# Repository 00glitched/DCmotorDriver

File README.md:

# DCmotorDriver
BDC motor driver based on N-MOSFET transistors H-bridge

Logical supply:

- 3V to 6V

Bootstrap:

- 10V to 20V
- 0A to 2A (current peak)

Power supply:

- 10V to 80V
- 0A to 3A (5A with dissipation)

## Material list
POWER:

- Driver IR2110 x2
- D FR107 x2
- C100uF electrolytic - 50V x2
- C47nF - 50V x2
- MOSFET IRF540N (or 520) x4
- D FR102 x4
- R10 x4

OTHERS:

- BJT BC635 (to 639) x2
- R10k x6
- C10uF - 250V
- C10uF - 10V
- C100uF - 50V

## Topology
- Driver 1: left-high-side + right-low-side

- Driver 2: right-high-side + left-low-side

## Images

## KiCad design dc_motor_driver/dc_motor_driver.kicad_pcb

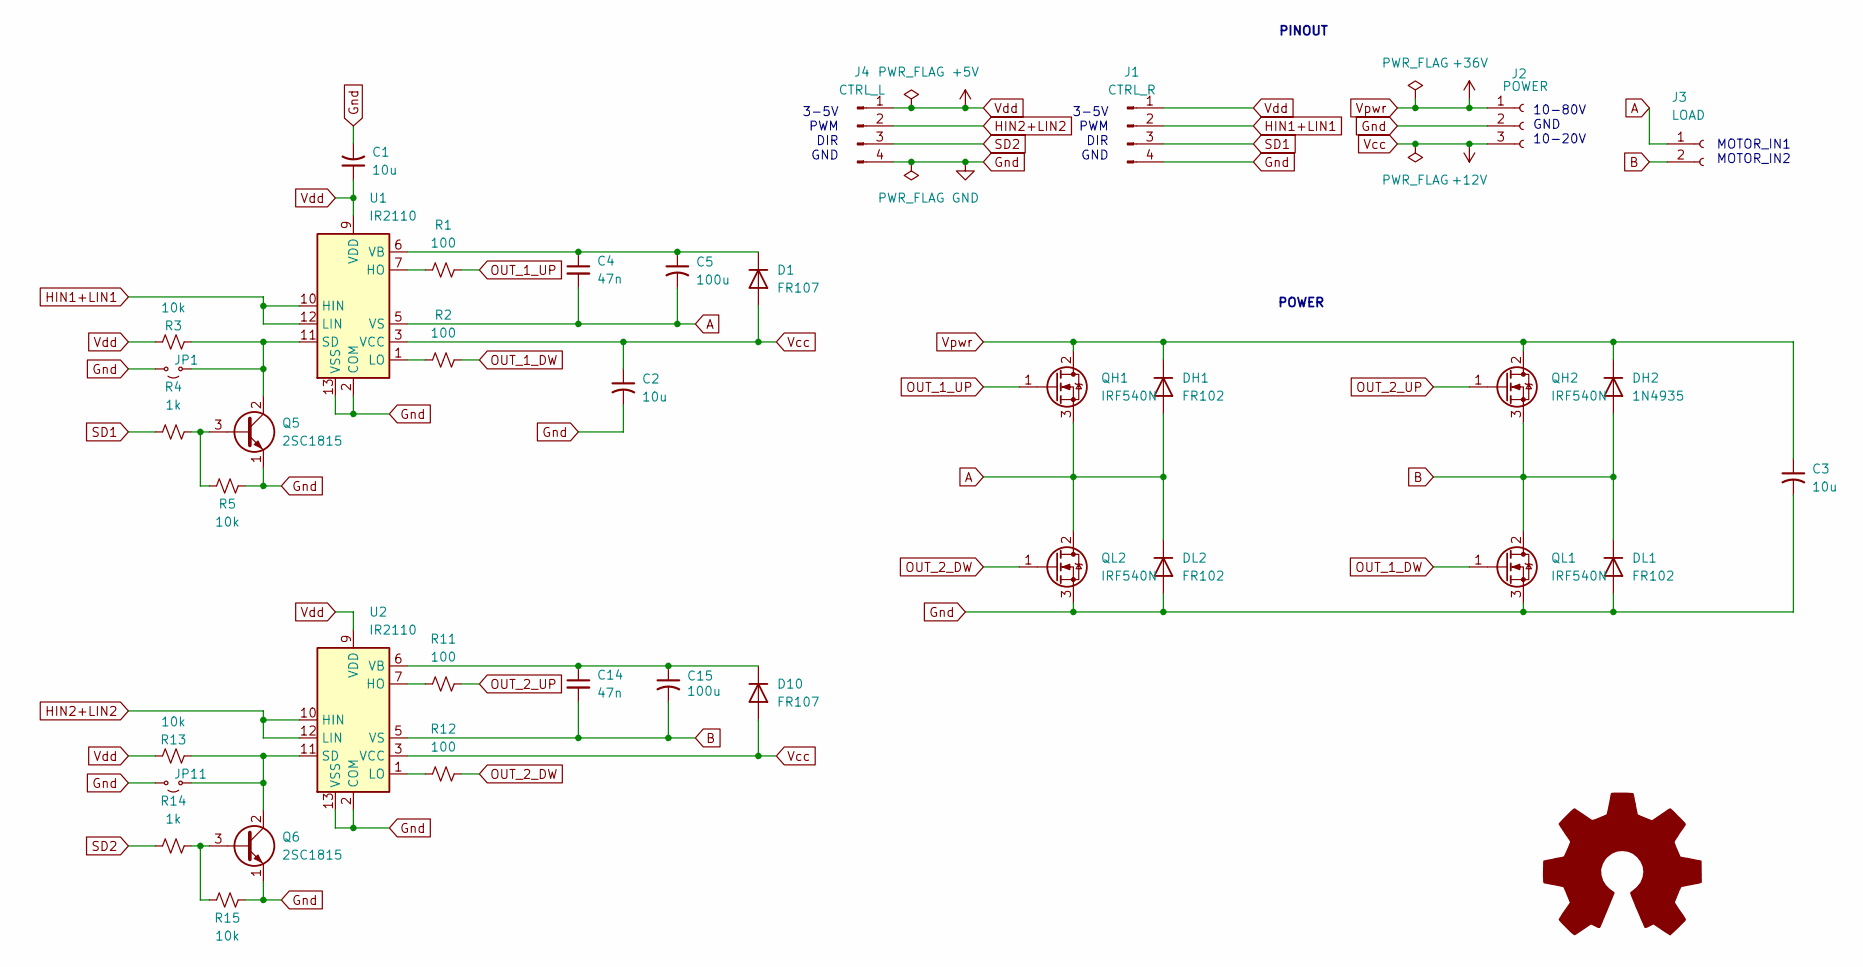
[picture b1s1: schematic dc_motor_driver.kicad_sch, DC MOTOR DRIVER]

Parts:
C1: 10u; CP_Radial_D5.0mm_P2.50mm
C2, C3: 10u; CP_Radial_D10.0mm_P2.50mm
C4, C14: 47n; C_Disc_D8.0mm_W5.0mm_P7.50mm
C5, C15: 100u; CP_Radial_D10.0mm_P2.50mm
D1, D10: FR107; D_DO-35_SOD27_P10.16mm_Horizontal
DH1: FR102; D_DO-41_SOD81_P10.16mm_Horizontal
DH2: 1N4935; D_DO-41_SOD81_P10.16mm_Horizontal
DL1, DL2: FR102; D_DO-41_SOD81_P10.16mm_Horizontal
J1: CTRL_R; PinHeader_1x04_P2.54mm_Vertical
J2: POWER; PinHeader_1x03_P2.54mm_Vertical
J3: LOAD; PinHeader_1x02_P2.54mm_Vertical
J4: CTRL_L; PinHeader_1x04_P2.54mm_Vertical
JP1, JP11: Jumper_2_Small_Open; PinHeader_2x01_P2.54mm_Vertical
OSHW1: Logo_Open_Hardware_Large; OSHW-Symbol_6.7x6mm_Copper
Q5, Q6: 2SC1815; TO-92_Wide
QH1, QH2: IRF540N; TO-220-3_Vertical
QL1, QL2: IRF540N; TO-220-3_Vertical
R1, R2, R11, R12: 100; R_Axial_DIN0207_L6.3mm_D2.5mm_P10.16mm_Horizontal
R3, R5, R13, R15: 10k; R_Axial_DIN0207_L6.3mm_D2.5mm_P10.16mm_Horizontal
R4, R14: 1k; R_Axial_DIN0207_L6.3mm_D2.5mm_P10.16mm_Horizontal
U1, U2: IR2110; DIP-14_W7.62mm_Socket

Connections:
A: C4.2, C5.2, DH1.2 (A), DL2.1 (K), J3.1, QH1.3 (S), QL2.2 (D), U1.5 (VS)
B: C14.2, C15.2, DH2.2 (A), DL1.1 (K), J3.2, QH2.3 (S), QL1.2 (D), U2.5 (VS)
Gnd: C1.2, C2.2, C3.2, DL1.2 (A), DL2.2 (A), J1.4, J2.2, J4.4, JP1.2 (B), JP11.2 (B), Q5.1 (E), Q6.1 (E), QL1.3 (S), QL2.3 (S), R5.1, R15.1, U1.2 (COM), U1.13 (VSS), U2.2 (COM), U2.13 (VSS)
HIN1+LIN1: J1.2, U1.10 (HIN), U1.12 (LIN)
HIN2+LIN2: J4.2, U2.10 (HIN), U2.12 (LIN)
unnamed: C4.1, C5.1, D1.1 (K), U1.6 (VB)
unnamed: C14.1, C15.1, D10.1 (K), U2.6 (VB)
unnamed: JP1.1 (A), Q5.2 (C), R3.2, U1.11 (SD)
unnamed: JP11.1 (A), Q6.2 (C), R13.2, U2.11 (SD)
unnamed: Q5.3 (B), R4.1, R5.2
unnamed: Q6.3 (B), R14.1, R15.2
unnamed: R1.1, U1.7 (HO)
unnamed: R2.1, U1.1 (LO)
unnamed: R11.1, U2.7 (HO)
unnamed: R12.1, U2.1 (LO)
OUT_1_DW: QL1.1 (G), R2.2
OUT_1_UP: QH1.1 (G), R1.2
OUT_2_DW: QL2.1 (G), R12.2
OUT_2_UP: QH2.1 (G), R11.2
SD1: J1.3, R4.2
SD2: J4.3, R14.2
Vcc: C2.1, D1.2 (A), D10.2 (A), J2.3, U1.3 (VCC), U2.3 (VCC)
Vdd: C1.1, J1.1, J4.1, R3.1, R13.1, U1.9 (VDD), U2.9 (VDD)
Vpwr: C3.1, DH1.1 (K), DH2.1 (K), J2.1, QH1.2 (D), QH2.2 (D)

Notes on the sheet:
3-5V PWM DIR GND
PINOUT
10-80V GND 10-20V
POWER
MOTOR_IN1 MOTOR_IN2

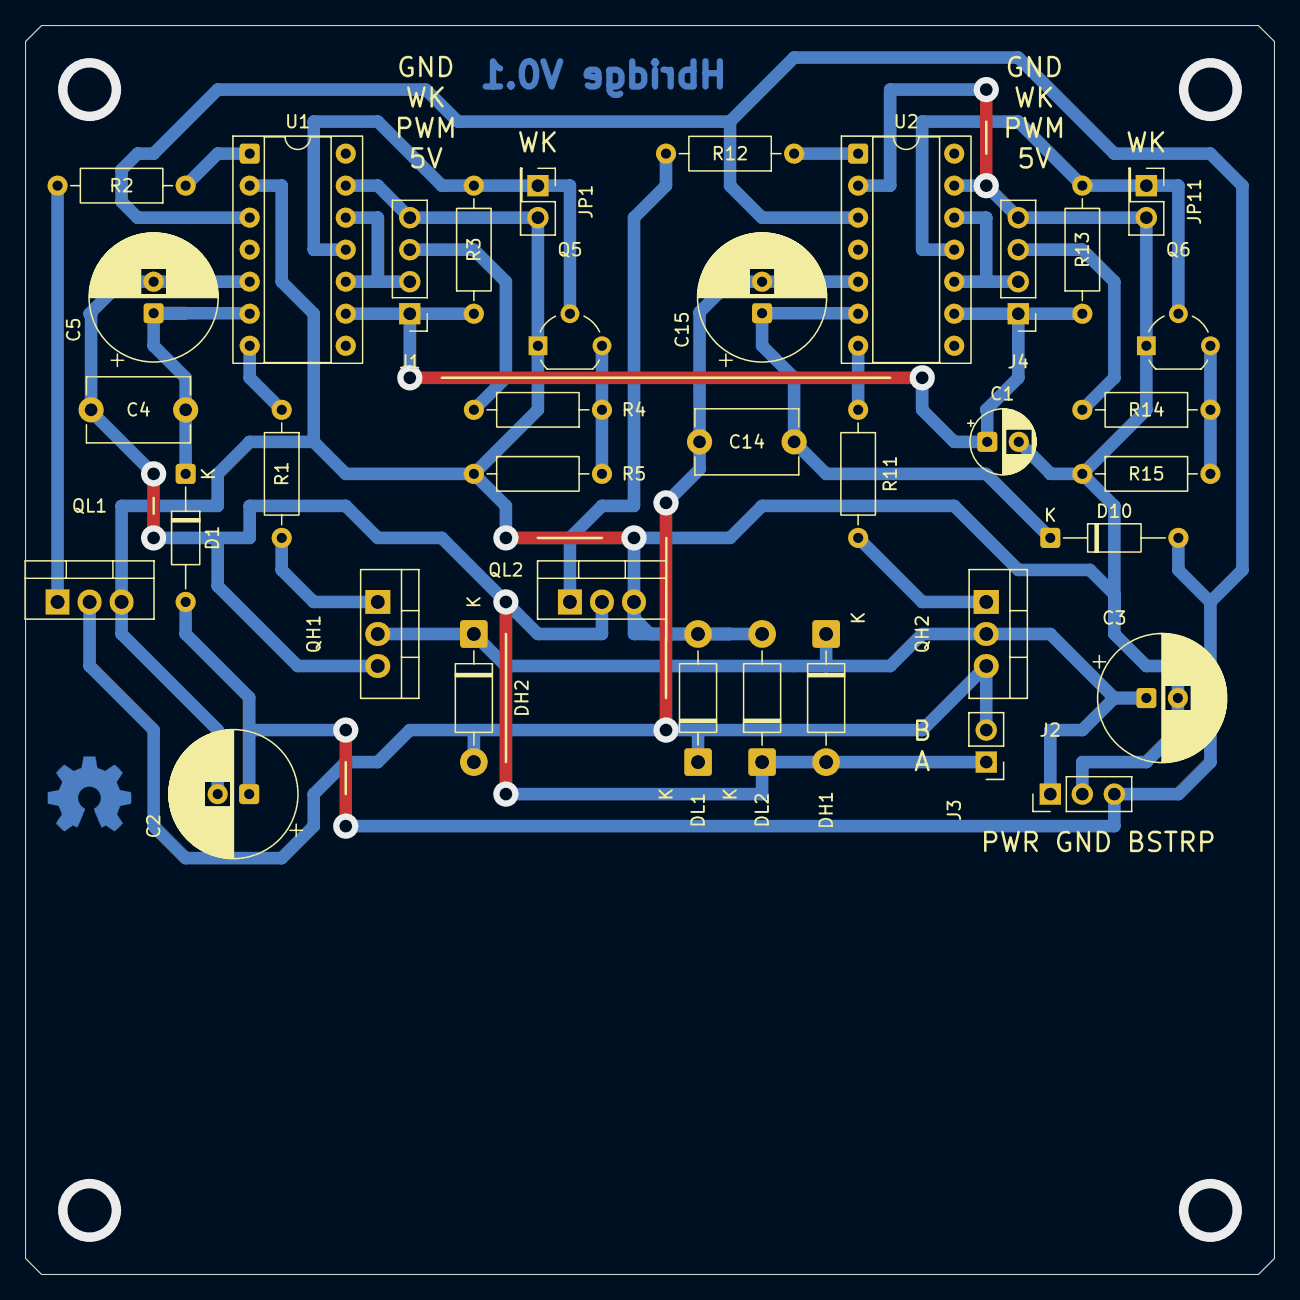
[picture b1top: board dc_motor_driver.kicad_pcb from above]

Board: 2 copper layers, 99.1 x 99.1 mm, 38 parts (1 on the bottom side), 24 nets.

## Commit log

2025-12-03 gitignore
2025-12-03 README
2025-12-03 KiCad: schem & PCB
2025-12-03 README: update
2025-12-03 IGNORE: release
